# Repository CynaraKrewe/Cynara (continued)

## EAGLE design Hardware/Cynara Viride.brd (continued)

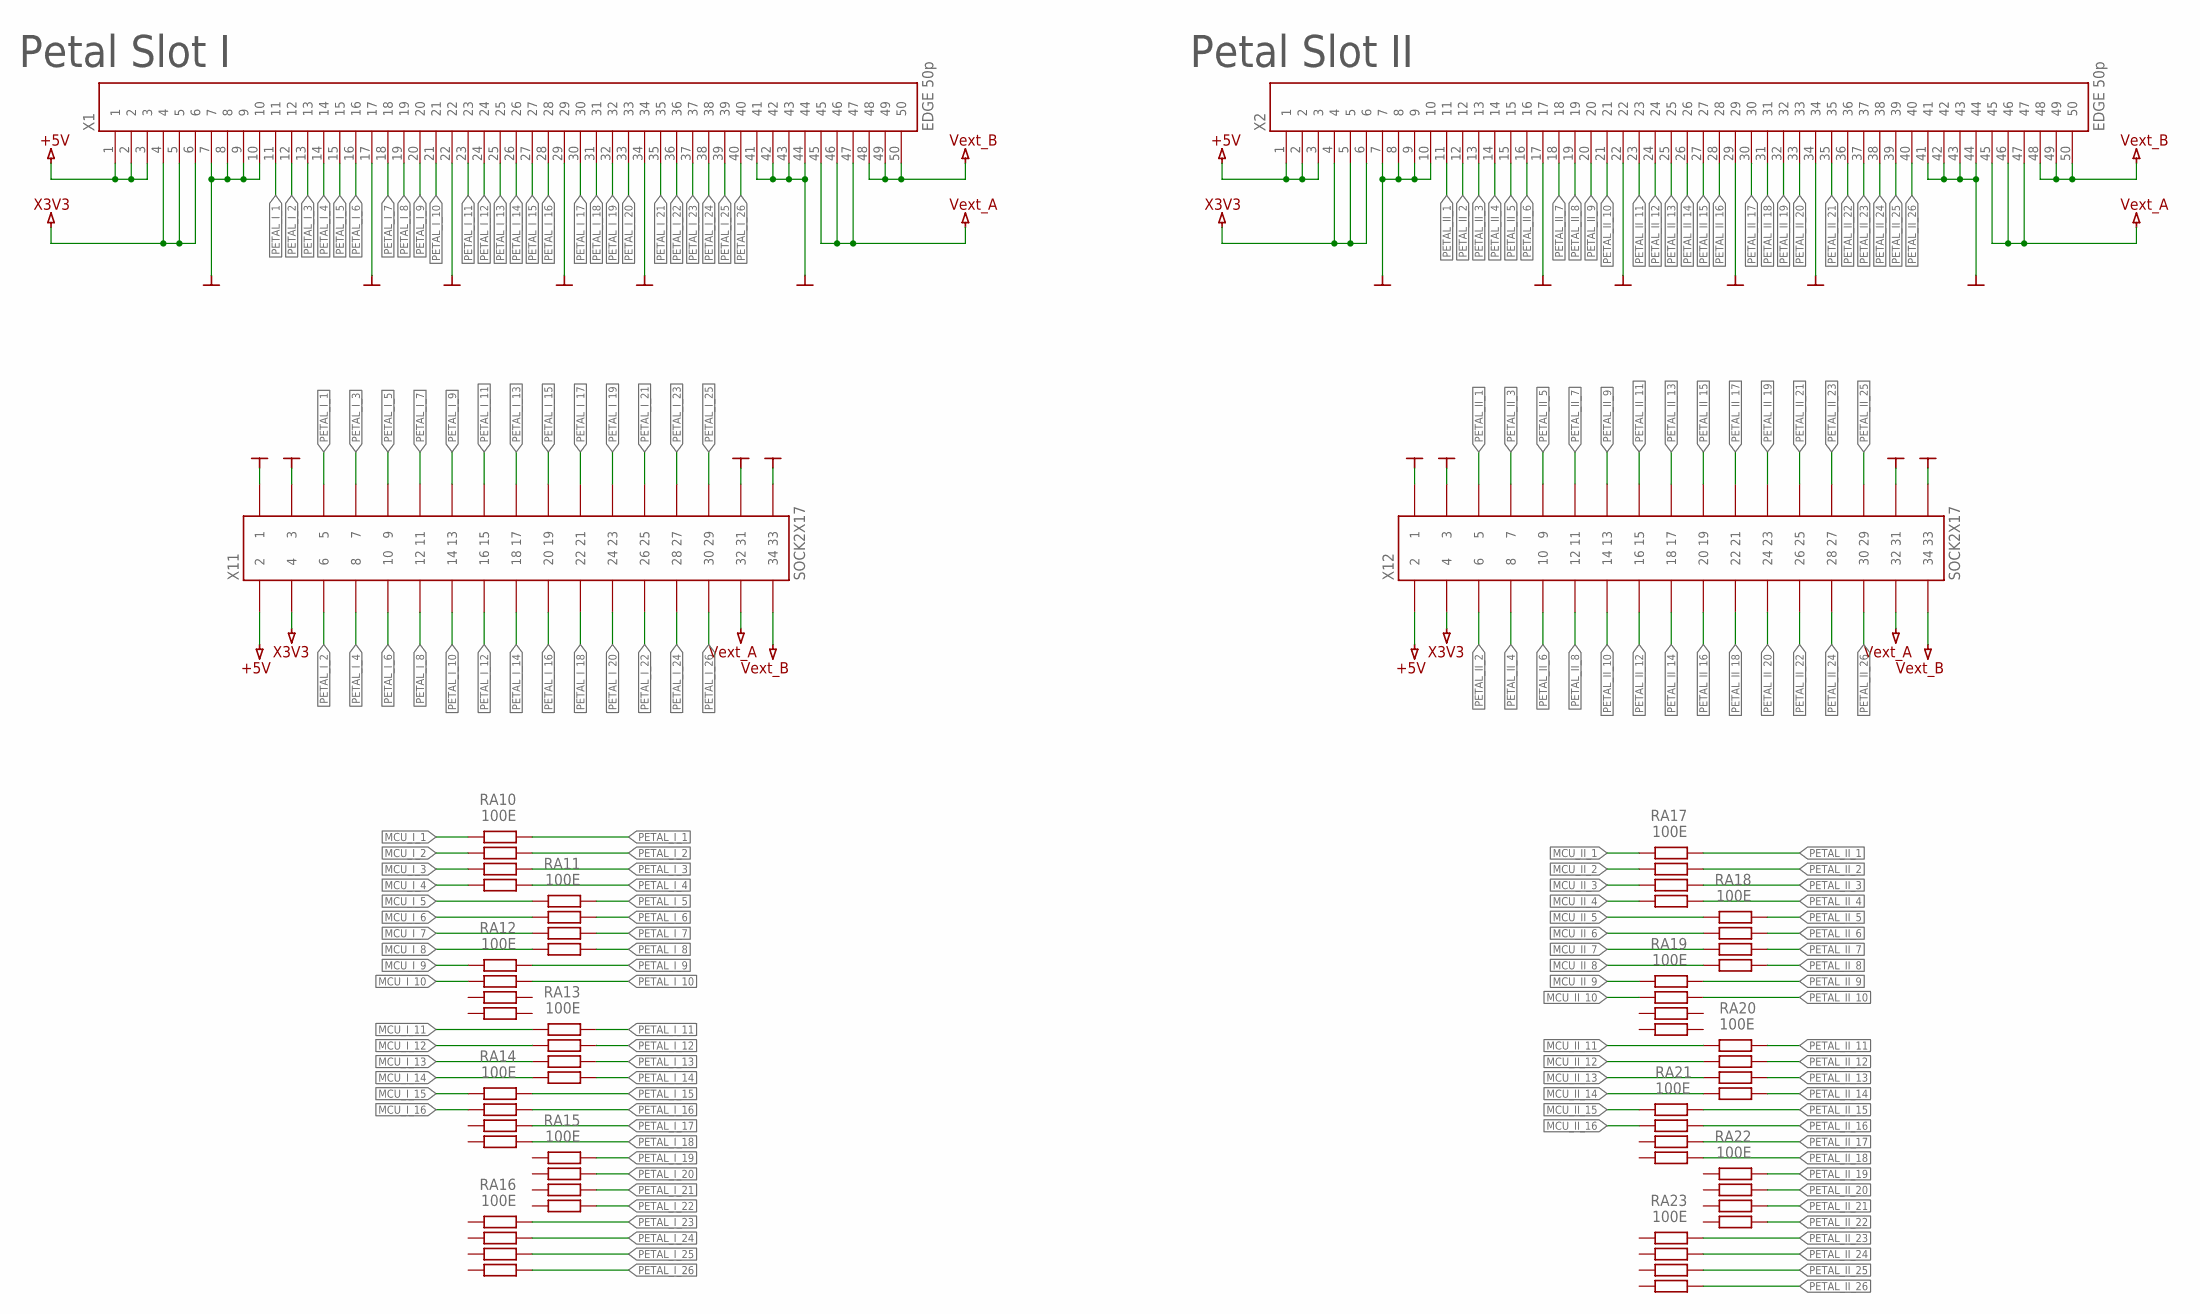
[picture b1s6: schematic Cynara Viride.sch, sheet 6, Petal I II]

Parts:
RA10, RA11, RA12, RA13, RA14, RA15, RA16, RA17, RA18, RA19, RA20, RA21, RA22, RA23: 100E; CRA06S
X1, X2: EDGE 50p; MB1-150-01-XX-S-XX-SL
X11, X12: SOCK2X17; 2X17P-FEMALE

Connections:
+5V: X1.1, X1.2, X1.3, X2.1, X2.2, X2.3, X11.2, X12.2; also elsewhere on the board
GND: X1.7, X1.8, X1.9, X1.10, X1.17, X1.22, X1.29, X1.34, X1.41, X1.42, X1.43, X1.44, X2.7, X2.8, X2.9, X2.10, X2.17, X2.22, X2.29, X2.34, X2.41, X2.42, X2.43, X2.44, X11.1, X11.3, X11.31, X11.33, X12.1, X12.3, X12.31, X12.33; also elsewhere on the board
MCU_II_1: RA17.1B; also elsewhere on the board
MCU_II_2: RA17.2B; also elsewhere on the board
MCU_II_3: RA17.3B; also elsewhere on the board
MCU_II_4: RA17.4B; also elsewhere on the board
MCU_II_5: RA18.1B; also elsewhere on the board
MCU_II_6: RA18.2B; also elsewhere on the board
MCU_II_7: RA18.3B; also elsewhere on the board
MCU_II_8: RA18.4B; also elsewhere on the board
MCU_II_9: RA19.1B; also elsewhere on the board
MCU_II_10: RA19.2B; also elsewhere on the board
MCU_II_11: RA20.1A; also elsewhere on the board
MCU_II_12: RA20.2A; also elsewhere on the board
MCU_II_13: RA20.3A; also elsewhere on the board
MCU_II_14: RA20.4A; also elsewhere on the board
MCU_II_15: RA21.1A; also elsewhere on the board
MCU_II_16: RA21.2A; also elsewhere on the board
MCU_I_1: RA10.1B; also elsewhere on the board
MCU_I_2: RA10.2B; also elsewhere on the board
MCU_I_3: RA10.3B; also elsewhere on the board
MCU_I_4: RA10.4B; also elsewhere on the board
MCU_I_5: RA11.1B; also elsewhere on the board
MCU_I_6: RA11.2B; also elsewhere on the board
MCU_I_7: RA11.3B; also elsewhere on the board
MCU_I_8: RA11.4B; also elsewhere on the board
MCU_I_9: RA12.1B; also elsewhere on the board
MCU_I_10: RA12.2B; also elsewhere on the board
MCU_I_11: RA13.1B; also elsewhere on the board
MCU_I_12: RA13.2B; also elsewhere on the board
MCU_I_13: RA13.3B; also elsewhere on the board
MCU_I_14: RA13.4B; also elsewhere on the board
MCU_I_15: RA14.1B; also elsewhere on the board
MCU_I_16: RA14.2B; also elsewhere on the board
PETAL_II_1: RA17.1A, X2.11, X12.5
PETAL_II_2: RA17.2A, X2.12, X12.6
PETAL_II_3: RA17.3A, X2.13, X12.7
PETAL_II_4: RA17.4A, X2.14, X12.8
PETAL_II_5: RA18.1A, X2.15, X12.9
PETAL_II_6: RA18.2A, X2.16, X12.10
PETAL_II_7: RA18.3A, X2.18, X12.11
PETAL_II_8: RA18.4A, X2.19, X12.12
PETAL_II_9: RA19.1A, X2.20, X12.13
PETAL_II_10: RA19.2A, X2.21, X12.14
PETAL_II_11: RA20.1B, X2.23, X12.15
PETAL_II_12: RA20.2B, X2.24, X12.16
PETAL_II_13: RA20.3B, X2.25, X12.17
PETAL_II_14: RA20.4B, X2.26, X12.18
PETAL_II_15: RA21.1B, X2.27, X12.19
PETAL_II_16: RA21.2B, X2.28, X12.20
PETAL_II_17: RA21.3B, X2.30, X12.21
PETAL_II_18: RA21.4B, X2.31, X12.22
PETAL_II_19: RA22.1A, X2.32, X12.23
PETAL_II_20: RA22.2A, X2.33, X12.24
PETAL_II_21: RA22.3A, X2.35, X12.25
PETAL_II_22: RA22.4A, X2.36, X12.26
PETAL_II_23: RA23.1A, X2.37, X12.27
PETAL_II_24: RA23.2A, X2.38, X12.28
PETAL_II_25: RA23.3A, X2.39, X12.29
PETAL_II_26: RA23.4A, X2.40, X12.30
PETAL_I_1: RA10.1A, X1.11, X11.5
PETAL_I_2: RA10.2A, X1.12, X11.6
PETAL_I_3: RA10.3A, X1.13, X11.7
PETAL_I_4: RA10.4A, X1.14, X11.8
PETAL_I_5: RA11.1A, X1.15, X11.9
PETAL_I_6: RA11.2A, X1.16, X11.10
PETAL_I_7: RA11.3A, X1.18, X11.11
PETAL_I_8: RA11.4A, X1.19, X11.12
PETAL_I_9: RA12.1A, X1.20, X11.13
PETAL_I_10: RA12.2A, X1.21, X11.14
PETAL_I_11: RA13.1A, X1.23, X11.15
PETAL_I_12: RA13.2A, X1.24, X11.16
PETAL_I_13: RA13.3A, X1.25, X11.17
PETAL_I_14: RA13.4A, X1.26, X11.18
PETAL_I_15: RA14.1A, X1.27, X11.19
PETAL_I_16: RA14.2A, X1.28, X11.20
PETAL_I_17: RA14.3A, X1.30, X11.21
PETAL_I_18: RA14.4A, X1.31, X11.22
PETAL_I_19: RA15.1A, X1.32, X11.23
PETAL_I_20: RA15.2A, X1.33, X11.24
PETAL_I_21: RA15.3A, X1.35, X11.25
PETAL_I_22: RA15.4A, X1.36, X11.26
PETAL_I_23: RA16.1A, X1.37, X11.27
PETAL_I_24: RA16.2A, X1.38, X11.28
PETAL_I_25: RA16.3A, X1.39, X11.29
PETAL_I_26: RA16.4A, X1.40, X11.30
VEXT_A: X1.45, X1.46, X1.47, X2.45, X2.46, X2.47, X11.32, X12.32; also elsewhere on the board
VEXT_B: X1.48, X1.49, X1.50, X2.48, X2.49, X2.50, X11.34, X12.34; also elsewhere on the board
X3V3: X1.4, X1.5, X1.6, X2.4, X2.5, X2.6, X11.4, X12.4; also elsewhere on the board

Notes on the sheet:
Petal Slot I
Petal Slot II

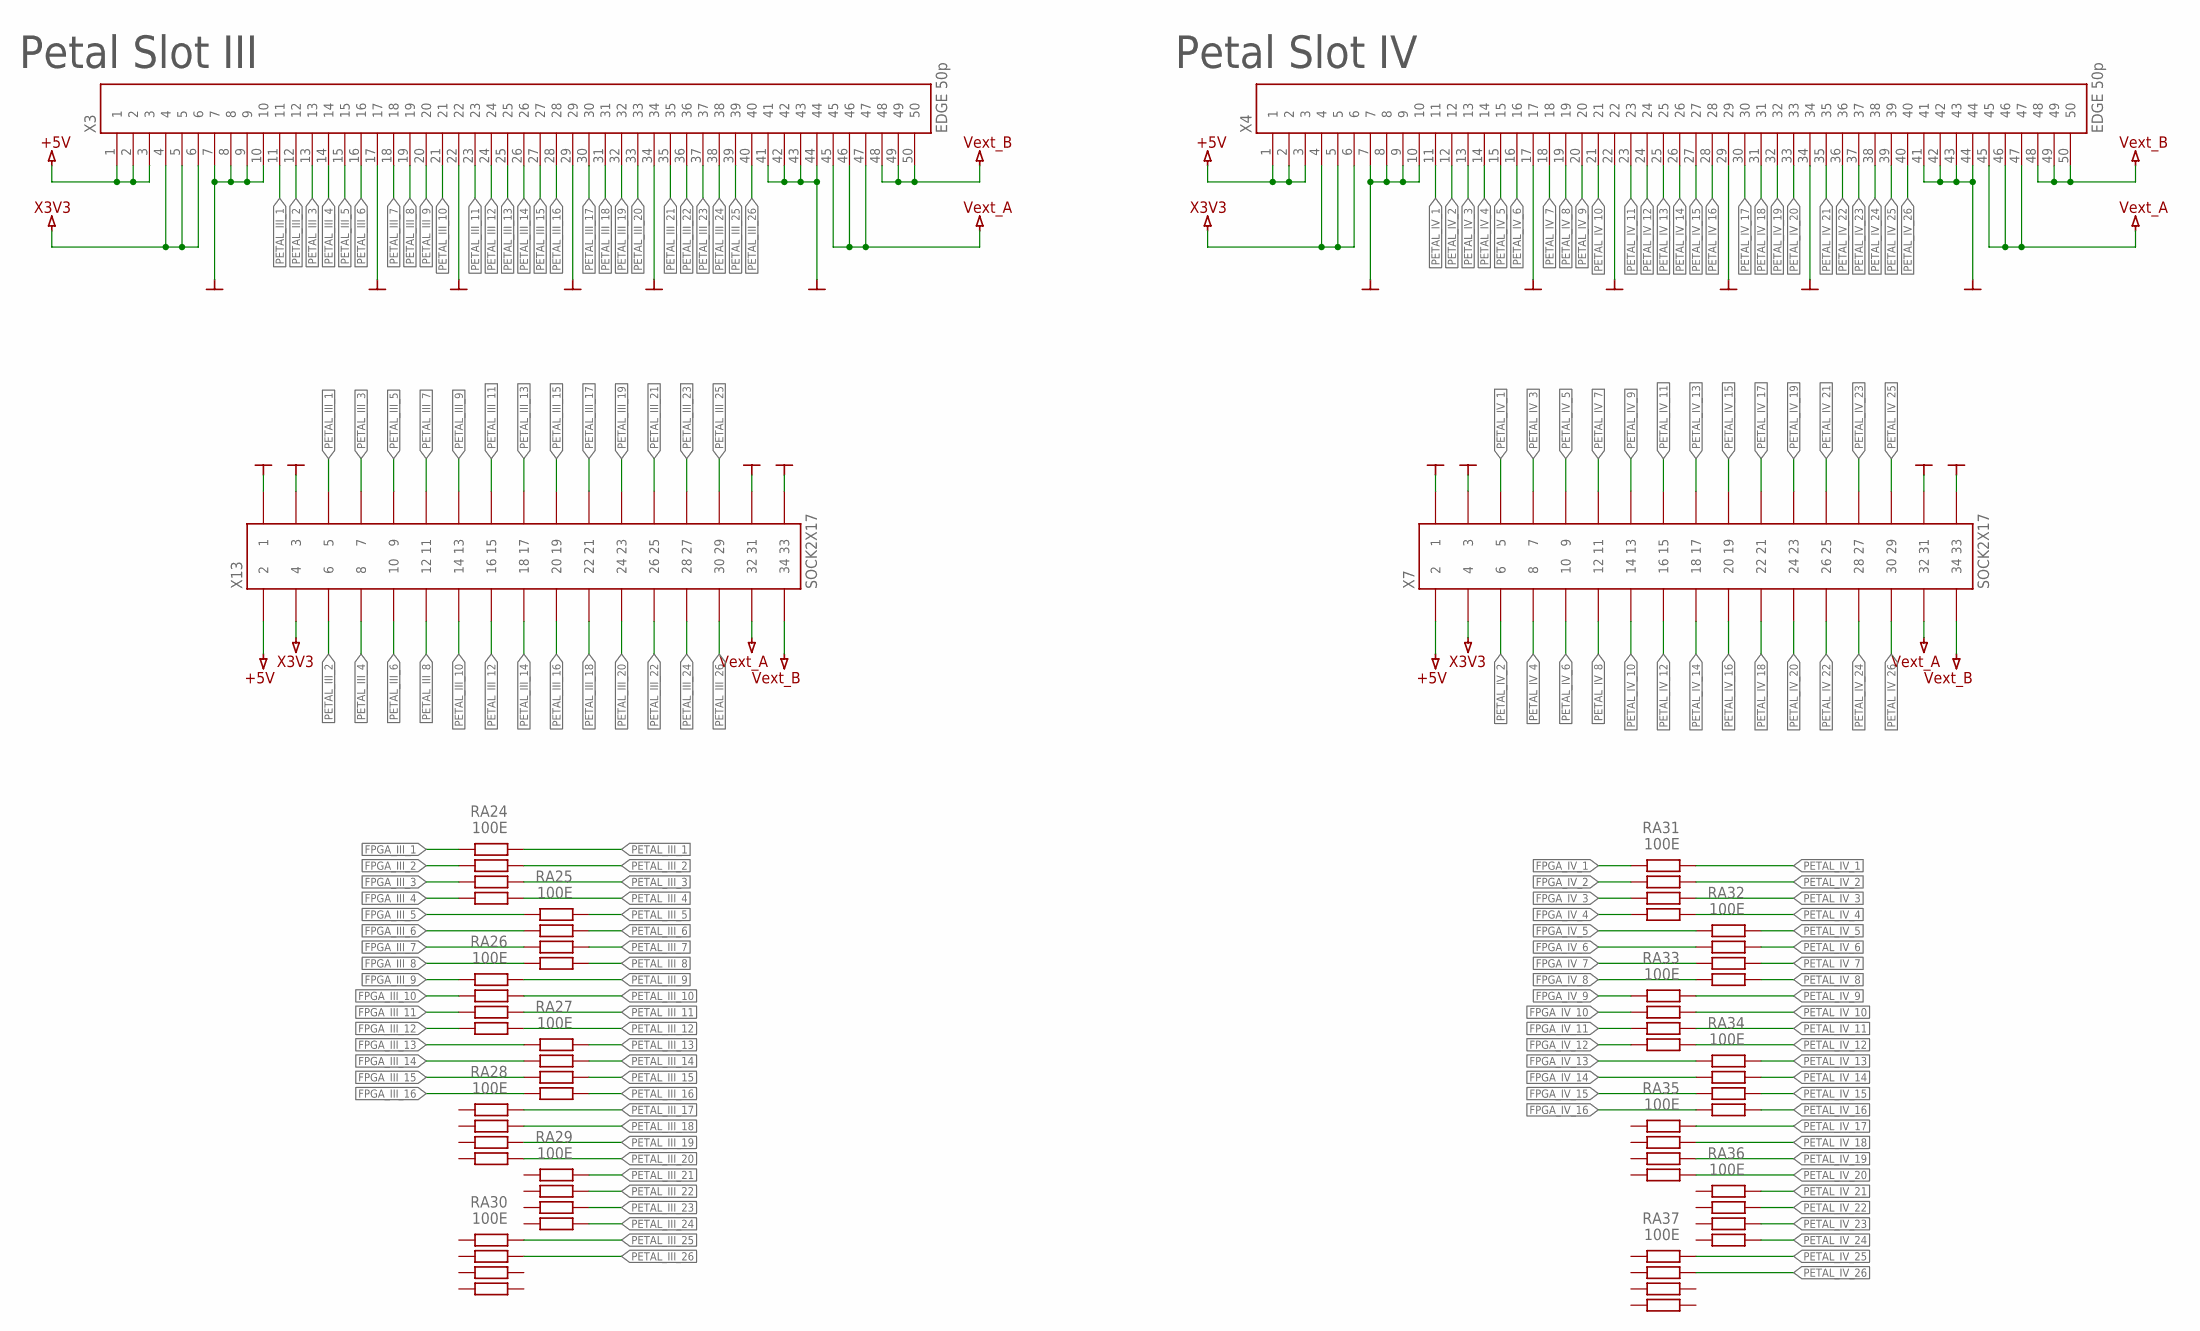
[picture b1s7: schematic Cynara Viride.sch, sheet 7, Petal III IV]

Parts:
RA24, RA25, RA26, RA27, RA28, RA29, RA30, RA31, RA32, RA33, RA34, RA35, RA36, RA37: 100E; CRA06S
X3, X4: EDGE 50p; MB1-150-01-XX-S-XX-SL
X7, X13: SOCK2X17; 2X17P-FEMALE

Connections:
+5V: X3.1, X3.2, X3.3, X4.1, X4.2, X4.3, X7.2, X13.2; also elsewhere on the board
FPGA_III_1: RA24.1B; also elsewhere on the board
FPGA_III_2: RA24.2B; also elsewhere on the board
FPGA_III_3: RA24.3B; also elsewhere on the board
FPGA_III_4: RA24.4B; also elsewhere on the board
FPGA_III_5: RA25.1B; also elsewhere on the board
FPGA_III_6: RA25.2B; also elsewhere on the board
FPGA_III_7: RA25.3B; also elsewhere on the board
FPGA_III_8: RA25.4B; also elsewhere on the board
FPGA_III_9: RA26.1B; also elsewhere on the board
FPGA_III_10: RA26.2B; also elsewhere on the board
FPGA_III_11: RA26.3B; also elsewhere on the board
FPGA_III_12: RA26.4B; also elsewhere on the board
FPGA_III_13: RA27.1B; also elsewhere on the board
FPGA_III_14: RA27.2B; also elsewhere on the board
FPGA_III_15: RA27.3B; also elsewhere on the board
FPGA_III_16: RA27.4B; also elsewhere on the board
FPGA_IV_1: RA31.1B; also elsewhere on the board
FPGA_IV_2: RA31.2B; also elsewhere on the board
FPGA_IV_3: RA31.3B; also elsewhere on the board
FPGA_IV_4: RA31.4B; also elsewhere on the board
FPGA_IV_5: RA32.1B; also elsewhere on the board
FPGA_IV_6: RA32.2B; also elsewhere on the board
FPGA_IV_7: RA32.3B; also elsewhere on the board
FPGA_IV_8: RA32.4B; also elsewhere on the board
FPGA_IV_9: RA33.1B; also elsewhere on the board
FPGA_IV_10: RA33.2B; also elsewhere on the board
FPGA_IV_11: RA33.3B; also elsewhere on the board
FPGA_IV_12: RA33.4B; also elsewhere on the board
FPGA_IV_13: RA34.1B; also elsewhere on the board
FPGA_IV_14: RA34.2B; also elsewhere on the board
FPGA_IV_15: RA34.3B; also elsewhere on the board
FPGA_IV_16: RA34.4B; also elsewhere on the board
GND: X3.7, X3.8, X3.9, X3.10, X3.17, X3.22, X3.29, X3.34, X3.41, X3.42, X3.43, X3.44, X4.7, X4.8, X4.9, X4.10, X4.17, X4.22, X4.29, X4.34, X4.41, X4.42, X4.43, X4.44, X7.1, X7.3, X7.31, X7.33, X13.1, X13.3, X13.31, X13.33; also elsewhere on the board
PETAL_III_1: RA24.1A, X3.11, X13.5
PETAL_III_2: RA24.2A, X3.12, X13.6
PETAL_III_3: RA24.3A, X3.13, X13.7
PETAL_III_4: RA24.4A, X3.14, X13.8
PETAL_III_5: RA25.1A, X3.15, X13.9
PETAL_III_6: RA25.2A, X3.16, X13.10
PETAL_III_7: RA25.3A, X3.18, X13.11
PETAL_III_8: RA25.4A, X3.19, X13.12
PETAL_III_9: RA26.1A, X3.20, X13.13
PETAL_III_10: RA26.2A, X3.21, X13.14
PETAL_III_11: RA26.3A, X3.23, X13.15
PETAL_III_12: RA26.4A, X3.24, X13.16
PETAL_III_13: RA27.1A, X3.25, X13.17
PETAL_III_14: RA27.2A, X3.26, X13.18
PETAL_III_15: RA27.3A, X3.27, X13.19
PETAL_III_16: RA27.4A, X3.28, X13.20
PETAL_III_17: RA28.1A, X3.30, X13.21
PETAL_III_18: RA28.2A, X3.31, X13.22
PETAL_III_19: RA28.3A, X3.32, X13.23
PETAL_III_20: RA28.4A, X3.33, X13.24
PETAL_III_21: RA29.1A, X3.35, X13.25
PETAL_III_22: RA29.2A, X3.36, X13.26
PETAL_III_23: RA29.3A, X3.37, X13.27
PETAL_III_24: RA29.4A, X3.38, X13.28
PETAL_III_25: RA30.1A, X3.39, X13.29
PETAL_III_26: RA30.2A, X3.40, X13.30
PETAL_IV_1: RA31.1A, X4.11, X7.5
PETAL_IV_2: RA31.2A, X4.12, X7.6
PETAL_IV_3: RA31.3A, X4.13, X7.7
PETAL_IV_4: RA31.4A, X4.14, X7.8
PETAL_IV_5: RA32.1A, X4.15, X7.9
PETAL_IV_6: RA32.2A, X4.16, X7.10
PETAL_IV_7: RA32.3A, X4.18, X7.11
PETAL_IV_8: RA32.4A, X4.19, X7.12
PETAL_IV_9: RA33.1A, X4.20, X7.13
PETAL_IV_10: RA33.2A, X4.21, X7.14
PETAL_IV_11: RA33.3A, X4.23, X7.15
PETAL_IV_12: RA33.4A, X4.24, X7.16
PETAL_IV_13: RA34.1A, X4.25, X7.17
PETAL_IV_14: RA34.2A, X4.26, X7.18
PETAL_IV_15: RA34.3A, X4.27, X7.19
PETAL_IV_16: RA34.4A, X4.28, X7.20
PETAL_IV_17: RA35.1A, X4.30, X7.21
PETAL_IV_18: RA35.2A, X4.31, X7.22
PETAL_IV_19: RA35.3A, X4.32, X7.23
PETAL_IV_20: RA35.4A, X4.33, X7.24
PETAL_IV_21: RA36.1A, X4.35, X7.25
PETAL_IV_22: RA36.2A, X4.36, X7.26
PETAL_IV_23: RA36.3A, X4.37, X7.27
PETAL_IV_24: RA36.4A, X4.38, X7.28
PETAL_IV_25: RA37.1A, X4.39, X7.29
PETAL_IV_26: RA37.2A, X4.40, X7.30
VEXT_A: X3.45, X3.46, X3.47, X4.45, X4.46, X4.47, X7.32, X13.32; also elsewhere on the board
VEXT_B: X3.48, X3.49, X3.50, X4.48, X4.49, X4.50, X7.34, X13.34; also elsewhere on the board
X3V3: X3.4, X3.5, X3.6, X4.4, X4.5, X4.6, X7.4, X13.4; also elsewhere on the board

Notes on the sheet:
Petal Slot IV
Petal Slot III

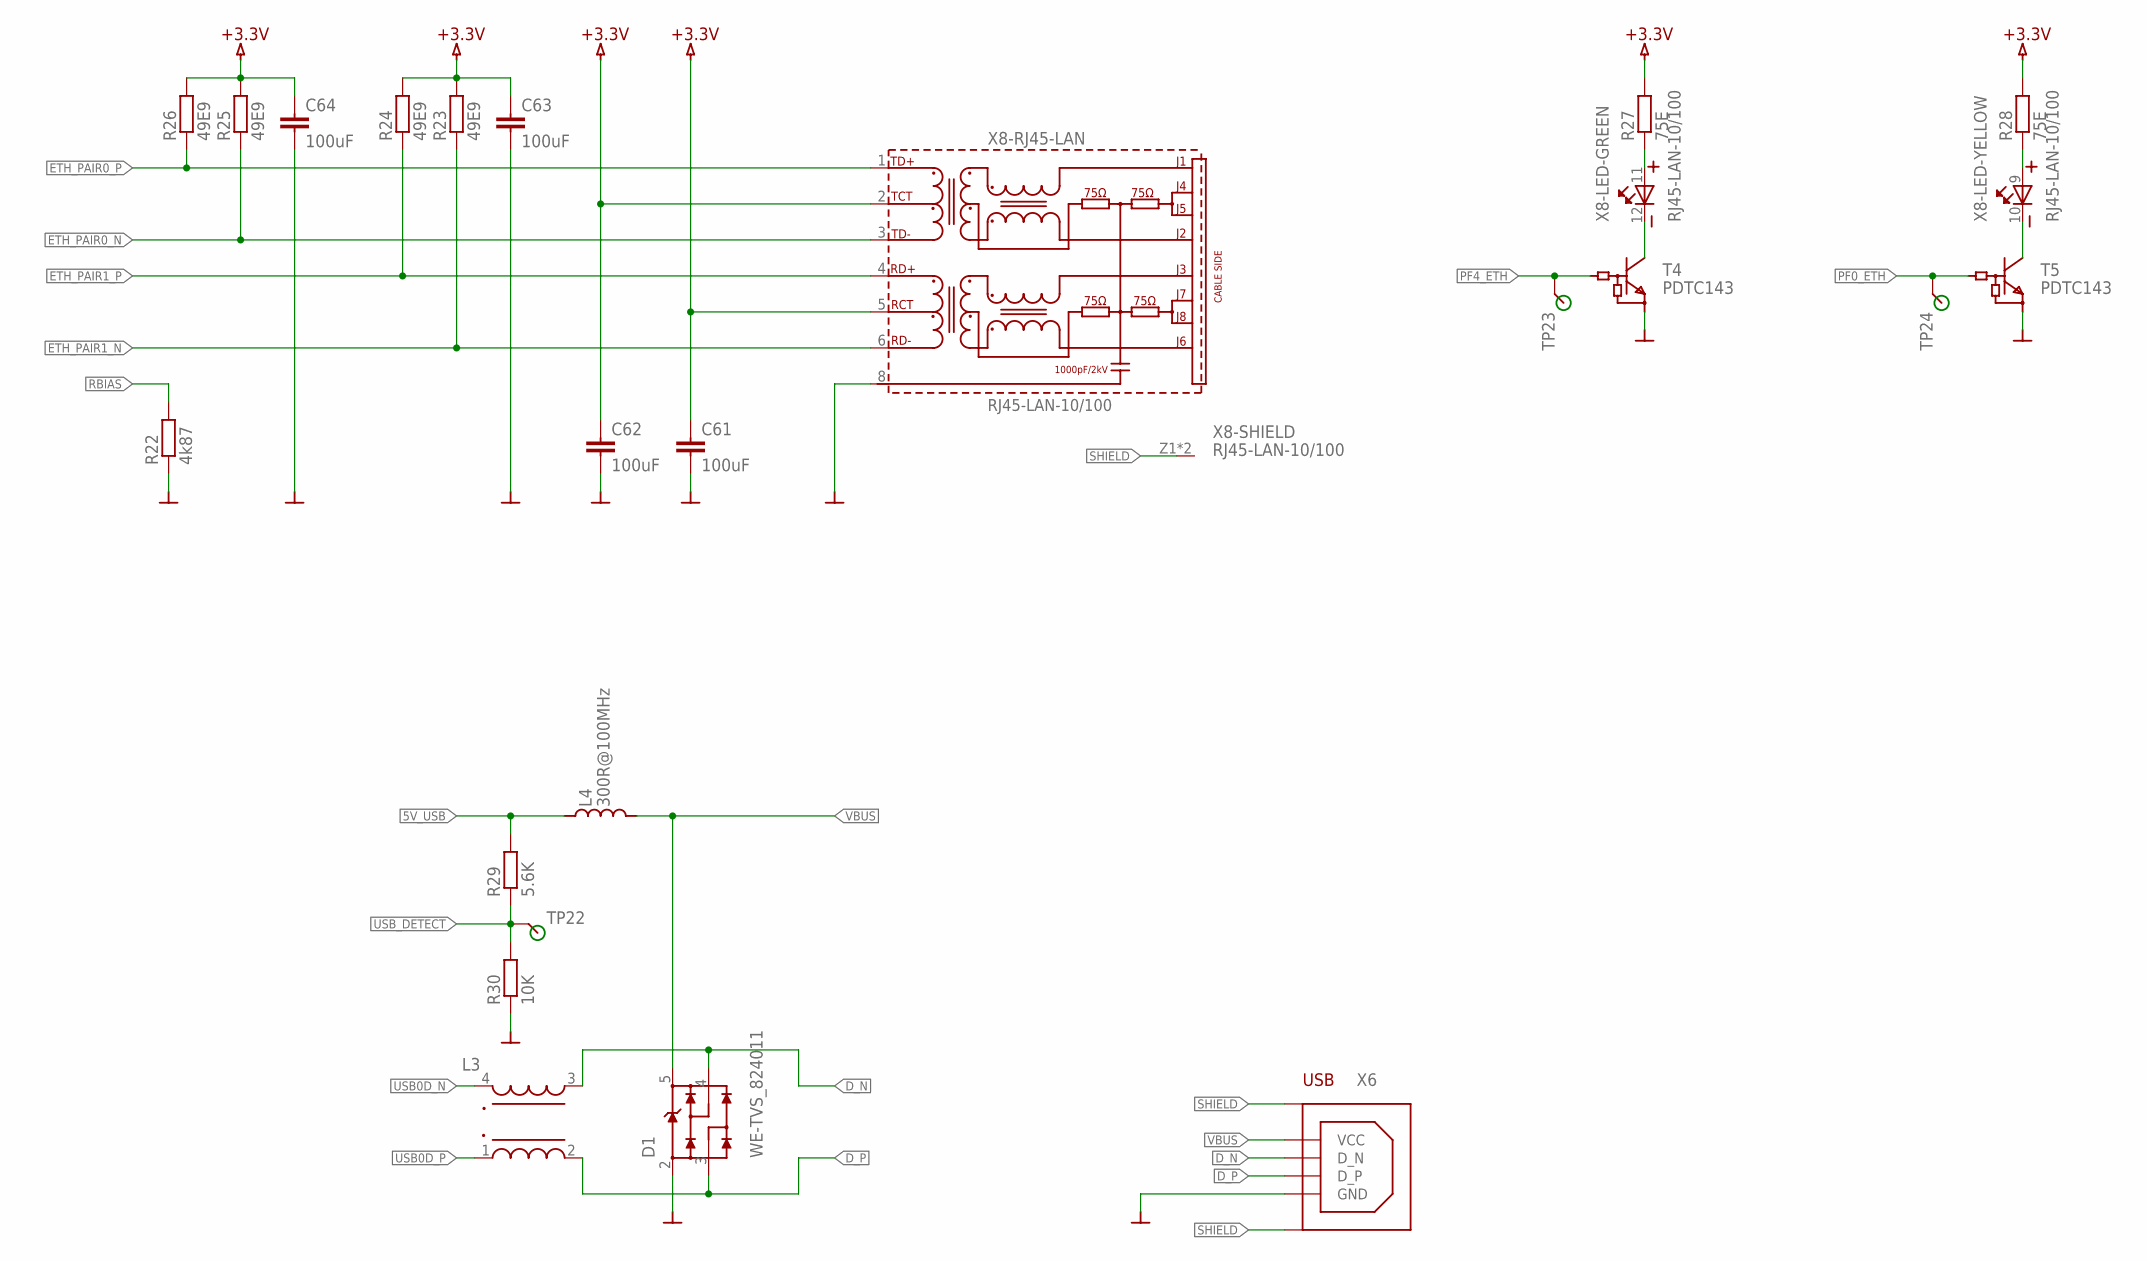
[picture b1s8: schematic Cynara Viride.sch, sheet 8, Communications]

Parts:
C61, C62, C63, C64: 100uF; C0603
D1: WE-TVS_824011; WE-TVS_SOT23-5L
L3: WE-CNSW_1206
L4: 300R@100MHz; L1608
R22: 4k87; R0603
R23, R24, R25, R26: 49E9; R0603
R27, R28: 75E; R0603
R29: 5.6K; R0603
R30: 10K; R0603
T4, T5: PDTC143; SOT23-3
TP22, TP23, TP24: TP-SMD
X6: 61400416121
X8: RJ45-LAN-10/100; 74990-WITH-LED-TYPE1

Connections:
5V_USB: L4.1 (E), R29.2; also elsewhere on the board
+3.3V: C61.1, C62.1, C63.1, C64.1, R23.2, R24.2, R25.2, R26.2, R27.2, R28.2, X8.2 (TCT), X8.5 (RCT); also elsewhere on the board
D_N: D1.4 (2), L3.3 (2), X6.2 (D_N)
D_P: D1.3 (1), L3.2 (3), X6.3 (D_P)
ETH_PAIR0_N: R25.1, X8.3 (TD-); also elsewhere on the board
ETH_PAIR0_P: R26.1, X8.1 (TD+); also elsewhere on the board
ETH_PAIR1_N: R23.1, X8.6 (RD-); also elsewhere on the board
ETH_PAIR1_P: R24.1, X8.4 (RD+); also elsewhere on the board
GND: C61.2, C62.2, C63.2, C64.2, D1.2 (GND), R22.1, R30.1, T4.2 (E), T5.2 (E), X6.4 (GND), X8.8 (SH); also elsewhere on the board
unnamed: R27.1, X8.11 (A)
unnamed: T4.3 (C), X8.12 (K)
unnamed: R28.1, X8.9 (A)
unnamed: T5.3 (C), X8.10 (K)
PF0_ETH: T5.1 (B), TP24.1; also elsewhere on the board
PF4_ETH: T4.1 (B), TP23.1; also elsewhere on the board
RBIAS: R22.2; also elsewhere on the board
SHIELD: X6.Z1 (GND), X6.Z2 (GND), X8.Z1, X8.Z2; also elsewhere on the board
USB0D_N: L3.4 (1); also elsewhere on the board
USB0D_P: L3.1 (4); also elsewhere on the board
USB_DETECT: R29.1, R30.2, TP22.1; also elsewhere on the board
VBUS: D1.5 (VDD), L4.2 (F), X6.1 (VCC)

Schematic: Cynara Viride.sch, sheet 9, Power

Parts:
C17, C43: 4u7; C0603
C18, C44: 1uF; C0603
C56, C57, C901, C902, C903, C904, C905, C906, C907: 100nF; C0603
G901, G902, G903, G904, G905, G906, G907: HOLE-3,5/6,6
J_1.2, J_3.3: HDR1X2; 1X2
L5: 26Z@100MHz; L1608
R901, R902, R903, R904, R905, R906, R907: 1M; R0603
SW2: 1XXX-MX-XX-C
TP1, TP2, TP3, TP4, TP5: TP-SMD
U2: MCP1826S 3V3; SOT-223
U6: MCP1826S 1V2; SOT-223
X5: MicroMatch 24; MICROMATCH-24-MALE

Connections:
5V_USB: SW2.1; also elsewhere on the board
+1.2V: J_1.2.1; also elsewhere on the board
+3.3V: J_3.3.1; also elsewhere on the board
+5V: C17.1, C43.1, C56.1, SW2.2, TP1.1, U2.1 (V_IN), U6.1 (V_IN); also elsewhere on the board
G901: C901.1, G901.1, R901.2
G902: C902.1, G902.1, R902.2
G903: C903.1, G903.1, R903.2
G904: C904.1, G904.1, R904.2
G905: C905.1, G905.1, R905.2
G906: C906.1, G906.1, R906.2
G907: C907.1, G907.1, R907.2
GND: C17.2, C18.2, C43.2, C44.2, C56.2, C57.2, C901.2, C902.2, C903.2, C904.2, C905.2, C906.2, C907.2, L5.1 (E), R901.1, R902.1, R903.1, R904.1, R905.1, R906.1, R907.1, TP4.1, TP5.1, U2.2 (GND), U2.4 (GND), U6.2 (GND), U6.4 (GND), X5.1, X5.3, X5.5, X5.7, X5.9, X5.11, X5.13, X5.15, X5.17, X5.19, X5.21, X5.23; also elsewhere on the board
unnamed: C18.1, C57.1, J_3.3.2, TP2.1, U2.3 (V_OUT)
unnamed: C44.1, J_1.2.2, TP3.1, U6.3 (V_OUT)
SHIELD: L5.2 (F); also elsewhere on the board
VEXT_A: X5.14, X5.16, X5.18; also elsewhere on the board
VEXT_B: X5.20, X5.22, X5.24; also elsewhere on the board
X3V3: X5.2, X5.4, X5.6; also elsewhere on the board
X5V: SW2.3, X5.8, X5.10, X5.12

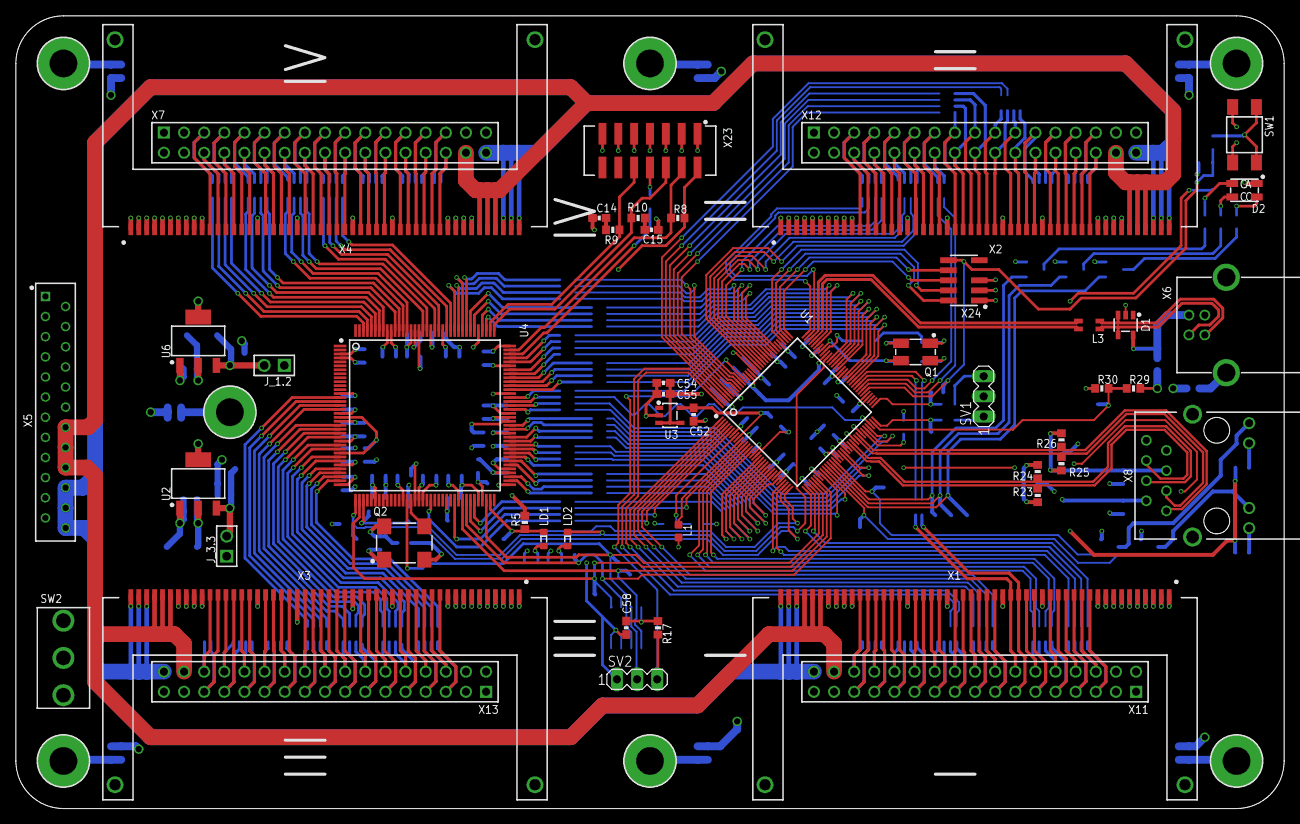
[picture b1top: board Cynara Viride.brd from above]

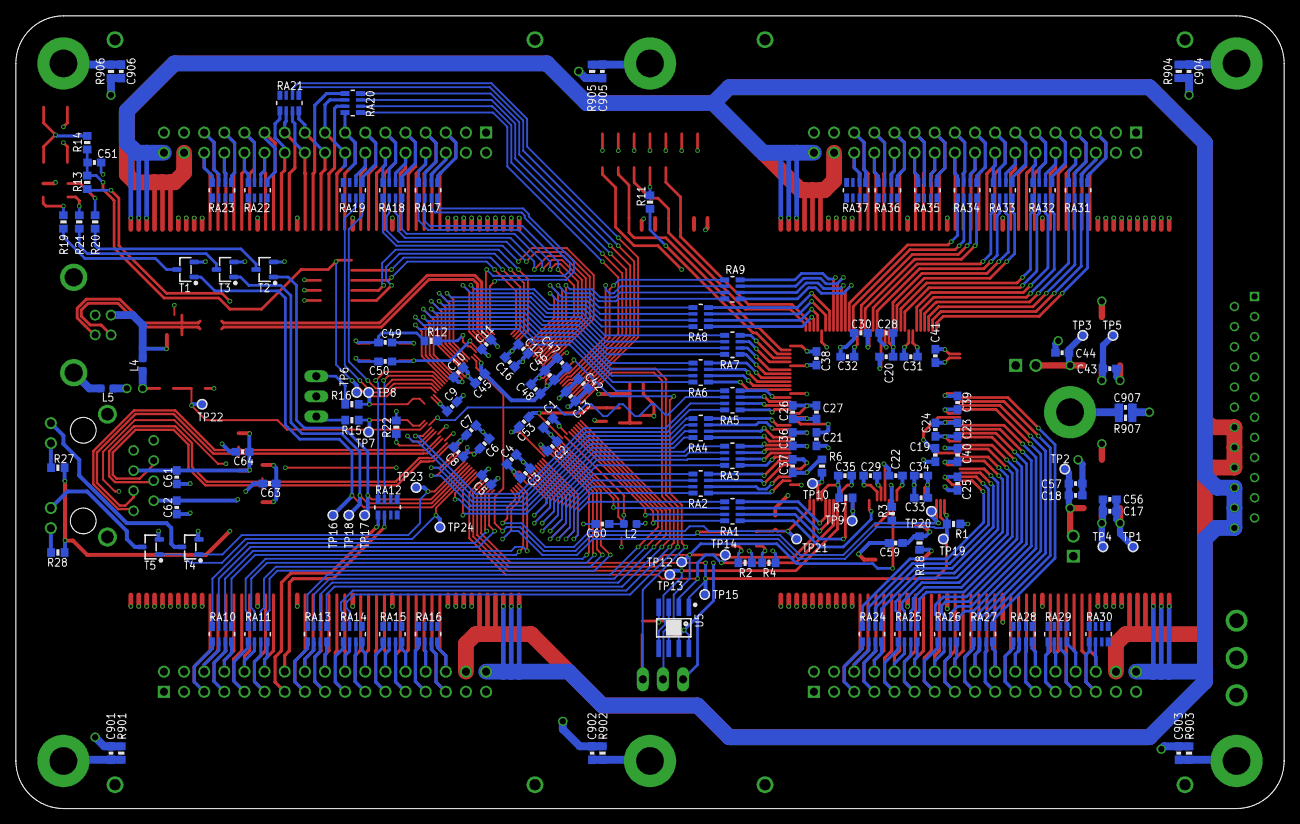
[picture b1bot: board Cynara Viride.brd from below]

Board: 4 copper layers, 160.0 x 100.0 mm, 217 parts (160 on the bottom side), 324 nets.

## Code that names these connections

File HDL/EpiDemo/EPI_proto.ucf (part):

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###################################################################################################################################################

NET "EPI0S[29]"	LOC = P104		| IOSTANDARD = LVCMOS33 | DRIVE = 8 | SLEW = FAST ; # Tiva PP2/103
NET "EPI0S[27]"	LOC = P101		| IOSTANDARD = LVCMOS33 | DRIVE = 8 | SLEW = FAST ; # Tiva PB2/91
NET "EPI0S[25]"	LOC = P99		| IOSTANDARD = LVCMOS33 | DRIVE = 8 | SLEW = FAST ; # Tiva PK6/61
NET "EPI0S[23]"	LOC = P97		| IOSTANDARD = LVCMOS33 | DRIVE = 8 | SLEW = FAST ; # Tiva PQ3/27

NET "EPI0S[31]"	LOC = P94		| IOSTANDARD = LVCMOS33 | DRIVE = 8 | SLEW = FAST ; # Tiva PK5/62
#TIMESPEC TS_CLK = PERIOD "EPI0S[31]" 1 MHz HIGH 50%;

#NET "RUPT[0]"	LOC = P92		| IOSTANDARD = LVCMOS33 | DRIVE = 8 | SLEW = FAST ; # Tiva PP0/118
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NET "EPI0S[17]"	LOC = P84		| IOSTANDARD = LVCMOS33 | DRIVE = 8 | SLEW = FAST ; # Tiva PL1/82
NET "EPI0S[15]"	LOC = P82		| IOSTANDARD = LVCMOS33 | DRIVE = 8 | SLEW = FAST ; # Tiva PM0/78
NET "EPI0S[13]"	LOC = P80		| IOSTANDARD = LVCMOS33 | DRIVE = 8 | SLEW = FAST ; # Tiva PM2/76
NET "EPI0S[3]"	LOC = P78		| IOSTANDARD = LVCMOS33 | DRIVE = 8 | SLEW = FAST ; # Tiva PK3/21
NET "EPI0S[2]"	LOC = P74		| IOSTANDARD = LVCMOS33 | DRIVE = 8 | SLEW = FAST ; # Tiva PK2/20
NET "EPI0S[1]"	LOC = P55		| IOSTANDARD = LVCMOS33 | DRIVE = 8 | SLEW = FAST ; # Tiva PK1/19
NET "EPI0S[0]"	LOC = P50		| IOSTANDARD = LVCMOS33 | DRIVE = 8 | SLEW = FAST ; # Tiva PK0/18
NET "EPI0S[7]"	LOC = P47		| IOSTANDARD = LVCMOS33 | DRIVE = 8 | SLEW = FAST ; # Tiva PC4/25
NET "EPI0S[5]"	LOC = P45		| IOSTANDARD = LVCMOS33 | DRIVE = 8 | SLEW = FAST ; # Tiva PC6/23
#NET ""	LOC = P43				| IOSTANDARD = LVCMOS33 | DRIVE = 8 | SLEW = FAST ; # NC

NET "EPI0S[30]"	LOC = P105		| IOSTANDARD = LVCMOS33 | DRIVE = 8 | SLEW = FAST ; # Tiva PP3/104
NET "EPI0S[28]"	LOC = P102		| IOSTANDARD = LVCMOS33 | DRIVE = 8 | SLEW = FAST ; # Tiva PB3/92
NET "EPI0S[26]"	LOC = P100		| IOSTANDARD = LVCMOS33 | DRIVE = 8 | SLEW = FAST ; # Tiva PL4/85
NET "EPI0S[24]"	LOC = P98		| IOSTANDARD = LVCMOS33 | DRIVE = 8 | SLEW = FAST ; # Tiva PK7/60
NET "EPI0S[22]"	LOC = P95		| IOSTANDARD = LVCMOS33 | DRIVE = 8 | SLEW = FAST ; # Tiva PQ2/11
NET "EPI0S[21]"	LOC = P93		| IOSTANDARD = LVCMOS33 | DRIVE = 8 | SLEW = FAST ; # Tiva PQ1/6
NET "EPI0S[20]"	LOC = P88		| IOSTANDARD = LVCMOS33 | DRIVE = 8 | SLEW = FAST ; # Tiva PQ0/5
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NET "EPI0S[16]"	LOC = P83		| IOSTANDARD = LVCMOS33 | DRIVE = 8 | SLEW = FAST ; # Tiva PL0/81
NET "EPI0S[14]"	LOC = P81		| IOSTANDARD = LVCMOS33 | DRIVE = 8 | SLEW = FAST ; # Tiva PM1/77
NET "EPI0S[12]"	LOC = P79		| IOSTANDARD = LVCMOS33 | DRIVE = 8 | SLEW = FAST ; # Tiva PM3/75
NET "EPI0S[11]"	LOC = P75		| IOSTANDARD = LVCMOS33 | DRIVE = 8 | SLEW = FAST ; # Tiva PG0/49
NET "EPI0S[10]"	LOC = P56		| IOSTANDARD = LVCMOS33 | DRIVE = 8 | SLEW = FAST ; # Tiva PG1/50
NET "EPI0S[9]"	LOC = P51		| IOSTANDARD = LVCMOS33 | DRIVE = 8 | SLEW = FAST ; # Tiva PA7/41
NET "EPI0S[8]"	LOC = P48		| IOSTANDARD = LVCMOS33 | DRIVE = 8 | SLEW = FAST ; # Tiva PA6/40
NET "EPI0S[6]"	LOC = P46		| IOSTANDARD = LVCMOS33 | DRIVE = 8 | SLEW = FAST ; # Tiva PC5/24 
NET "EPI0S[4]"	LOC = P44		| IOSTANDARD = LVCMOS33 | DRIVE = 8 | SLEW = FAST ; # Tiva PC7/22

###################################################################################################################################################
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
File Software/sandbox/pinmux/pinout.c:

//*****************************************************************************
//
// Configure the device pins for different signals
//
// Copyright (C) 2014 Texas Instruments Incorporated - http://www.ti.com/ 
// 
// 
//  Redistribution and use in source and binary forms, with or without 
//  modification, are permitted provided that the following conditions 
//  are met:
//
//    Redistributions of source code must retain the above copyright 
//    notice, this list of conditions and the following disclaimer.
//
//    Redistributions in binary form must reproduce the above copyright
//    notice, this list of conditions and the following disclaimer in the 
//    documentation and/or other materials provided with the   
//    distribution.
//
//    Neither the name of Texas Instruments Incorporated nor the names of
//    its contributors may be used to endorse or promote products derived
//    from this software without specific prior written permission.
//
//  THIS SOFTWARE IS PROVIDED BY THE COPYRIGHT HOLDERS AND CONTRIBUTORS 
//  "AS IS" AND ANY EXPRESS OR IMPLIED WARRANTIES, INCLUDING, BUT NOT 
//  LIMITED TO, THE IMPLIED WARRANTIES OF MERCHANTABILITY AND FITNESS FOR
//  A PARTICULAR PURPOSE ARE DISCLAIMED. IN NO EVENT SHALL THE COPYRIGHT 
//  OWNER OR CONTRIBUTORS BE LIABLE FOR ANY DIRECT, INDIRECT, INCIDENTAL, 
//  SPECIAL, EXEMPLARY, OR CONSEQUENTIAL DAMAGES (INCLUDING, BUT NOT 
//  LIMITED TO, PROCUREMENT OF SUBSTITUTE GOODS OR SERVICES; LOSS OF USE,
//  DATA, OR PROFITS; OR BUSINESS INTERRUPTION) HOWEVER CAUSED AND ON ANY
//  THEORY OF LIABILITY, WHETHER IN CONTRACT, STRICT LIABILITY, OR TORT 
//  (INCLUDING NEGLIGENCE OR OTHERWISE) ARISING IN ANY WAY OUT OF THE USE 
//  OF THIS SOFTWARE, EVEN IF ADVISED OF THE POSSIBILITY OF SUCH DAMAGE.
//
//*****************************************************************************

// This file was automatically generated on 19-10-2016 at 13:08:09
// by TI PinMux version 
//
//*****************************************************************************

#include <stdbool.h>
#include <stdint.h>
#include "inc/hw_gpio.h"
#include "inc/hw_memmap.h"
#include "inc/hw_types.h"
#include "driverlib/gpio.h"
#include "driverlib/pin_map.h"
#include "driverlib/rom.h"
#include "driverlib/rom_map.h"
#include "driverlib/sysctl.h"
#include "pinout.h"

//*****************************************************************************
//
//! \addtogroup pinout_api
//! @{
//
//*****************************************************************************

//*****************************************************************************
//
//! Configures the device pins for the customer specific usage.
//!
//! \return None.
//
//*****************************************************************************
void
PinoutSet(void)
{
    //
    // Enable Peripheral Clocks 
    //
	MAP_SysCtlPeripheralEnable(SYSCTL_PERIPH_GPIOA);
	MAP_SysCtlPeripheralEnable(SYSCTL_PERIPH_GPIOF);
	MAP_SysCtlPeripheralEnable(SYSCTL_PERIPH_GPIOJ);
	MAP_SysCtlPeripheralEnable(SYSCTL_PERIPH_GPION);

    //
    // Configure the GPIO Pin Mux for PF0
	// for M0PWM0
    //
	MAP_GPIOPinConfigure(GPIO_PF0_M0PWM0);
	MAP_GPIOPinTypePWM(GPIO_PORTF_BASE, GPIO_PIN_0);

    //
    // Configure the GPIO Pin Mux for PJ0
	// for GPIO_PJ0
    //
	MAP_GPIOPinTypeGPIOInput(GPIO_PORTJ_BASE, GPIO_PIN_0);
	MAP_GPIOPadConfigSet(GPIO_PORTJ_BASE, GPIO_PIN_0, GPIO_STRENGTH_2MA, GPIO_PIN_TYPE_STD_WPU);

    //
    // Configure the GPIO Pin Mux for PJ1
	// for GPIO_PJ1
    //
	MAP_GPIOPinTypeGPIOInput(GPIO_PORTJ_BASE, GPIO_PIN_1);
	MAP_GPIOPadConfigSet(GPIO_PORTJ_BASE, GPIO_PIN_1, GPIO_STRENGTH_2MA, GPIO_PIN_TYPE_STD_WPU);

    //
    // Configure the GPIO Pin Mux for PN1
	// for GPIO_PN1
    //
	MAP_GPIOPinTypeGPIOOutput(GPIO_PORTN_BASE, GPIO_PIN_1);

    //
    // Configure the GPIO Pin Mux for PN0
	// for GPIO_PN0
    //
	MAP_GPIOPinTypeGPIOOutput(GPIO_PORTN_BASE, GPIO_PIN_0);

    //
    // Configure the GPIO Pin Mux for PF4
	// for GPIO_PF4
    //
	MAP_GPIOPinTypeGPIOOutput(GPIO_PORTF_BASE, GPIO_PIN_4);

    //
    // Configure the GPIO Pin Mux for PA0
	// for U0RX
    //
	MAP_GPIOPinConfigure(GPIO_PA0_U0RX);
	MAP_GPIOPinTypeUART(GPIO_PORTA_BASE, GPIO_PIN_0);

    //
    // Configure the GPIO Pin Mux for PA1
	// for U0TX
    //
	MAP_GPIOPinConfigure(GPIO_PA1_U0TX);
	MAP_GPIOPinTypeUART(GPIO_PORTA_BASE, GPIO_PIN_1);

}

//*****************************************************************************
//
// Close the Doxygen group.
//! @}
//
//*****************************************************************************

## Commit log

2016-05-06 Update LICENSE
    Changed license to cover both software and hardware.
2016-05-06 Added logo instead of regular title.
2016-05-11 Added krewe members.
2016-05-11 Added pin and interconnect descriptions.
2016-05-12 Migrated all pictures from the Subversion repository.
2016-05-18 Added Cynara carrier schematic and layout.
2016-05-19 Migrated doumentation from Subversion.
2016-05-19 Updated readme with ideas and goals. Removed the members, this can be seen in the Cynara Krewe organization on github.
2016-05-24 [WIP] Moved FPGA and MCU to make space for Ethernet and USB.
2016-05-25 Layout for Ethernet and USB 2.0. Fixed problem with VREFA+ being too close to EPI clock signal.
2016-05-27 Updated documentation. Added information about trace lengths of the EPI bus. Minor fixes in pictures.
2016-05-28 FPGA and C's around the FPGA are snapped to grid again. Small reroute of USB differential pair.
2016-05-28 Fixed trace width and spacing issue after reroute of USB differential pair.
2016-05-28 All Petals are connected in the layout.
2016-05-29 Added proposal for power routing to the Petals.
2016-06-01 updated imperial values of pcb build-up
2016-06-01 Completed routing for the power rails.
2016-06-08 Added VBUS detect circuitry. Drill size of mounting holes is 3.5 mm to fit M3 bolts.
2016-06-11 Proper mounting holes. Small change in layout of +1.2V plane. Enhanced USB connector symbol. Added shield conenctions.
2016-06-29 Changed microcontroller symbol to one a functional and power part. Renamed Petal signals. Shield for Ethernet and USB is a polygon now.
2016-06-29 Added jumpers to disconnect the different power rails.
2016-07-12 Added more test points.
2016-07-12 Renamed pin mux configuration.
2016-07-15 Added blinky (target is EK-TM4C129EXL for now).
2016-07-18 Added license header to file.
2016-07-18 Rename.
2016-07-18 Added USB library.
2016-07-18 Cleanup.
2016-07-18 Added CppUTest library.
2016-07-18 Fixed path afer rename.
2016-07-26 Blinky supports controlling GPIO by means of JSON over the UART. Cleaned up startup and linker script.
2016-07-27 Added missing change in TivaWare debug header.
2016-07-27 Removed warning in Release build. Added appropriate C bindings to TivaWare debug header.
2016-07-28 Moved flow and tm4c specific features to their respective directories.
2016-07-28 Minor fixes.
2016-07-28 Added tests for flow using CppUTest library.
2016-07-29 Added tests for connections and ports.
2016-07-29 Added tests for Invert and Toggle components.
2016-09-02 Added more tests for Flow.
2016-09-22 Blinky includes a USB CDC connection with registered VID/PID codes. Timer component now runs in systick interrupt context.
2016-09-23 Use the Pin Mux Tool to generate the pin mux configuration.
2016-10-04 Switches control the timer period in the blinky application.
2016-10-19 Cleaned up slikscreen in board layout. Moved tm4c components to their own header/source. Added basic PWM component.
2016-10-27 Added PWM on one of the LEDs of the EK-TM4C129EXL.
2016-10-27 Blinky is just blinky.
2016-10-27 Moved flow and tm4c source code so it can be shared between projects.
2016-10-27 Added missing include path.
2016-10-27 Fixed projects.
2016-10-27 Removed USB library from blinky.
2016-10-27 Fixed unit test project for flow.
2016-10-27 Added sandbox project.
2016-10-27 Cleaned up blinky.
2016-10-28 Added inter-project dependencies for correct build order. Added debug functionality to Flow. TM4C UART component is configurable.
2016-11-29 Added documentation for Cynara Flow (Software).
2017-04-18 Added user constraints for proto setup.
2017-04-29 Added EPI demo HDL project.
2017-04-29 Made latch generic.
2017-04-29 Made latch generic. Added missing project change.
2017-07-08 Initial add of the SuperDongle KiCad project.
2017-07-08 Added IC lib + start of micro dongle
2017-07-09 added USB connector
2017-07-09 added usb footprint
